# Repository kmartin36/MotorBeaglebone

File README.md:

# MotorBeaglebone
Motor drive cape for the Beaglebone Black featuring three channels, encoders, current sensors, and voltage sensing

This uses the High-Res PWM modules, the ADC, and the Enhanced Quadrature Encoder inputs.

See [this](https://github.com/Teknoman117/beaglebot/tree/master/encoders) repo for information on using the EQEP modules.

The new version is designed in kicad which features six channels and makes use of the DRV8873 motor driver IC. The three remaining quadrature encoder channels routed to the PRU pins for software decoding.

There is also a design based on the PocketBeagle with only four motors as the PocketBeagle only provies four of the 6 PWM modules on header pins.

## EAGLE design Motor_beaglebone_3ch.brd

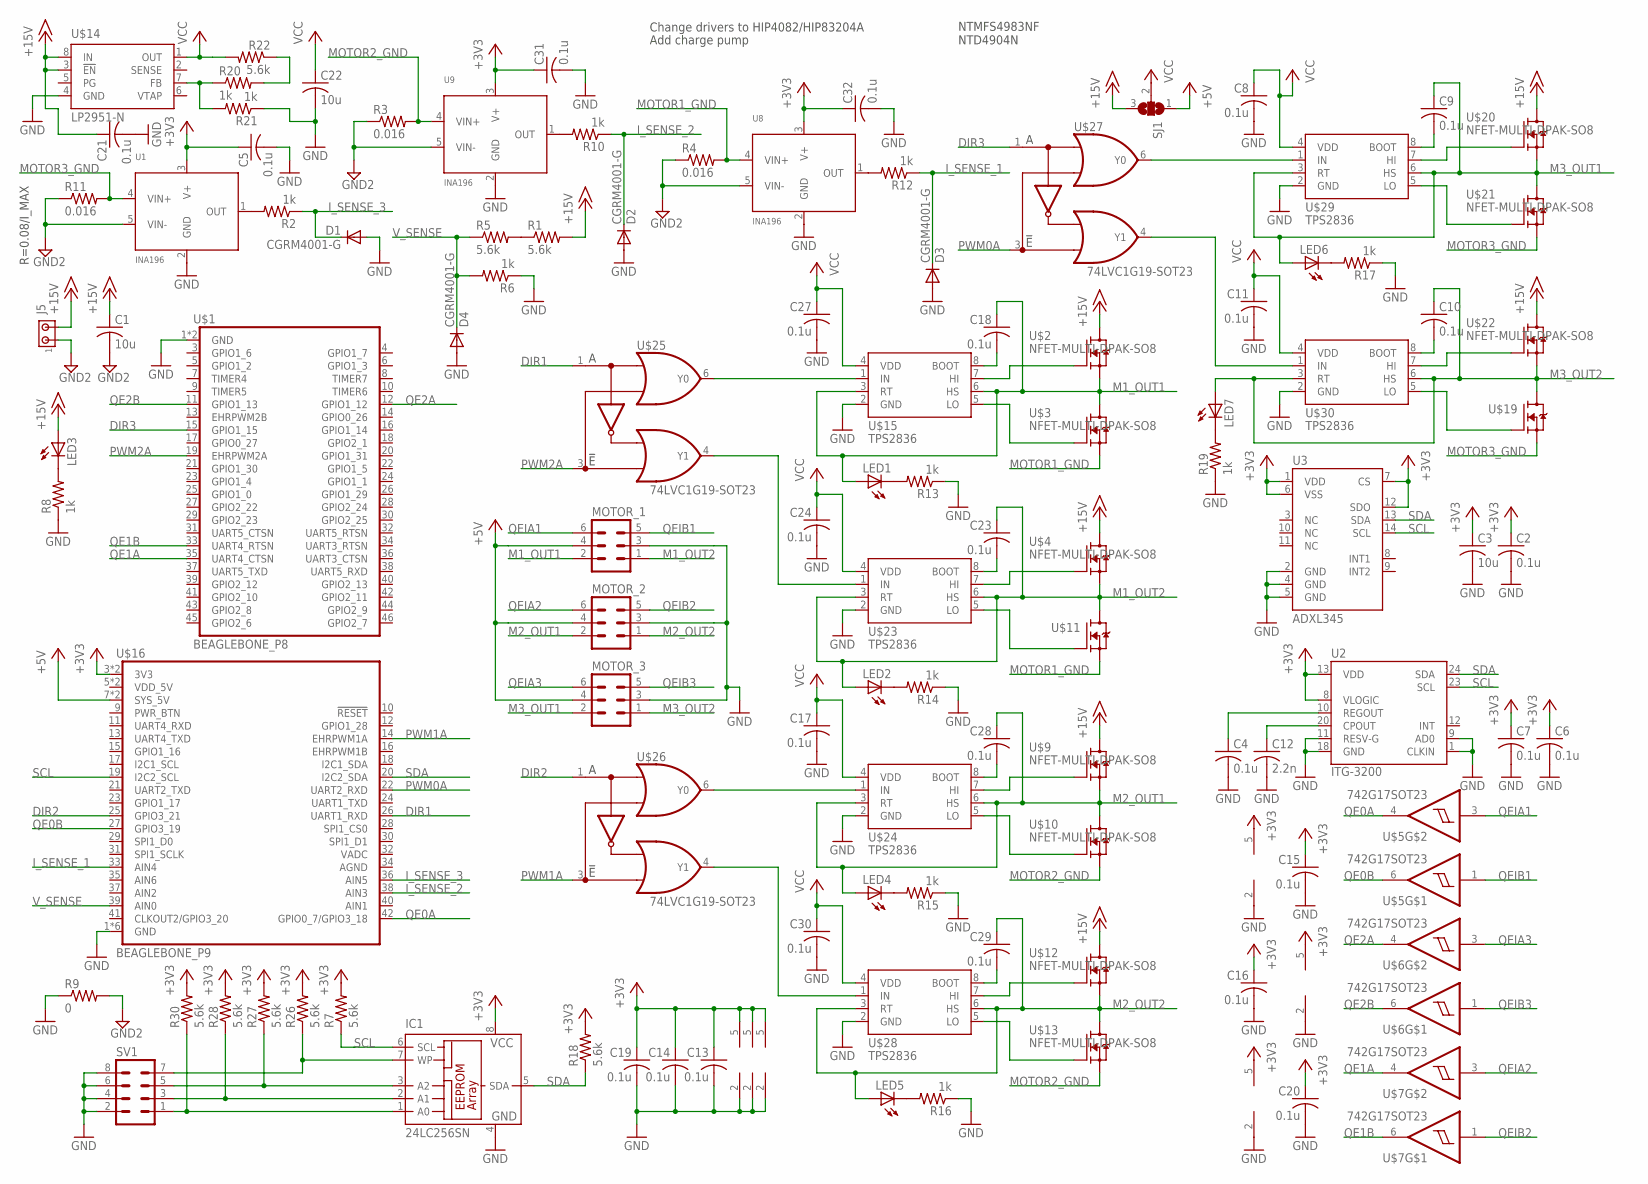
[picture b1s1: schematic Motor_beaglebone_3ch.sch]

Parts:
C1, C3, C22: 10u; C1206
C2, C4, C5, C6, C7, C8, C9, C10, C11, C13, C14, C15, C16, C17, C18, C19, C20, C21, C23, C24, C27, C28, C29, C30, C31, C32: 0.1u; C0603
C12: 2.2n; C0603
D1, D2, D3, D4: CGRM4001-G; SOD-123_MINI-SMA
IC1: 24LC256SN; SO-08
J5: MTA02-156; 1X2MTA
LED1, LED2, LED3, LED4, LED5, LED6, LED7: LED0603; LED-0603
MOTOR_1, MOTOR_2, MOTOR_3: MA03-2
R1, R5, R7, R18, R22, R26, R27, R28, R30: 5.6k; C0603
R2, R6, R8, R10, R12, R13, R14, R15, R16, R17, R19, R20, R21: 1k; C0603
R3, R4, R11: 0.016; C1206
R9: 0; C0603
SJ1: SJ2W; SJ_2
SV1: MA04-2
U1, U8, U9: INA196; SOT23-5
U2: ITG-3200; QFN-24
U3: ADXL345; LGA14
U$1: BEAGLEBONE_P8
U$2, U$3, U$4, U$9, U$10, U$11, U$12, U$13, U$19, U$20, U$21, U$22: NFET-MULTI-DPAK-SO8; DPAK-S08
U$5, U$6, U$7: 742G17SOT23; SOT23-6
U$14: LP2951-N; VSSOP8
U$15, U$23, U$24, U$28, U$29, U$30: TPS2836; SO-08
U$16: BEAGLEBONE_P9
U$25, U$26, U$27: 74LVC1G19-SOT23; SOT23-6

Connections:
+3V3: C2.1, C3.1, C5.1, C6.1, C7.1, C13.1, C14.1, C15.1, C16.1, C19.1, C20.1, C31.1, C32.1, IC1.8 (VCC), R7.2, R18.2, R26.2, R27.2, R28.2, R30.2, U1.3 (V+), U2.8 (VLOGIC), U2.13 (VDD), U3.1 (VDD), U3.6 (VSS), U3.7 (CS), U3.12 (SDO), U8.3 (V+), U9.3 (V+), U$5.5 (V+), U$6.5 (V+), U$7.5 (V+), U$16.3 (3V3), U$16.4 (3V3), U$25.5 (V+), U$26.5 (V+), U$27.5 (V+)
+5V: MOTOR_1.4, MOTOR_2.4, MOTOR_3.4, SJ1.1, U$16.7 (SYS_5V), U$16.8 (SYS_5V)
+15V: C1.1, C21.1, J5.2, LED3.A, R1.2, SJ1.3, U$2.2 (D), U$4.2 (D), U$9.2 (D), U$12.2 (D), U$14.3 (!EN), U$14.8 (IN), U$20.2 (D), U$22.2 (D)
DIR1: U$16.26 (UART1_RXD), U$25.1 (A)
DIR2: U$16.25 (GPIO3_21), U$26.1 (A)
DIR3: U$1.15 (GPIO1_15), U$27.1 (A)
GND: C2.2, C3.2, C4.2, C5.2, C6.2, C7.2, C8.2, C11.2, C12.2, C13.2, C14.2, C15.2, C16.2, C17.2, C19.2, C20.2, C21.2, C22.2, C24.2, C27.2, C30.2, C31.2, C32.2, D1.A, D2.A, D3.A, D4.A, IC1.4 (GND), MOTOR_1.3, MOTOR_2.3, MOTOR_3.3, R6.1, R8.1, R9.1, R13.1, R14.1, R15.1, R16.1, R17.1, R19.1, R21.1, SV1.2, SV1.4, SV1.6, SV1.8, U1.2 (GND), U2.1 (CLKIN), U2.9 (AD0), U2.11 (RESV-G), U2.18 (GND), U3.2 (GND), U3.4 (GND), U3.5 (GND), U8.2 (GND), U9.2 (GND), U$1.1 (GND), U$1.2 (GND), U$5.2 (V-), U$6.2 (V-), U$7.2 (V-), U$14.4 (GND), U$15.2 (GND), U$16.1 (GND), U$16.2 (GND), U$16.43 (GND), U$16.44 (GND), U$16.45 (GND), U$16.46 (GND), U$23.2 (GND), U$24.2 (GND), U$25.2 (V-), U$26.2 (V-), U$27.2 (V-), U$28.2 (GND), U$29.2 (GND), U$30.2 (GND)
GND2: C1.2, J5.1, R3.1, R4.1, R9.2, R11.1, U1.5 (VIN-), U8.5 (VIN-), U9.5 (VIN-)
I_SENSE_1: D3.C, R12.1, U$16.33 (AIN4)
I_SENSE_2: D2.C, R10.1, U$16.38 (AIN3)
I_SENSE_3: D1.C, R2.1, U$16.36 (AIN5)
M1_OUT1: C18.1, LED1.A, MOTOR_1.2, U$2.3 (S), U$2.4 (S), U$2.5 (S), U$2.6 (S), U$3.2 (D), U$15.3 (RT), U$15.6 (HS)
M1_OUT2: C23.1, LED2.A, MOTOR_1.1, U$4.3 (S), U$4.4 (S), U$4.5 (S), U$4.6 (S), U$11.2 (D), U$23.3 (RT), U$23.6 (HS)
M2_OUT1: C28.1, LED4.A, MOTOR_2.2, U$9.3 (S), U$9.4 (S), U$9.5 (S), U$9.6 (S), U$10.2 (D), U$24.3 (RT), U$24.6 (HS)
M2_OUT2: C29.1, LED5.A, MOTOR_2.1, U$12.3 (S), U$12.4 (S), U$12.5 (S), U$12.6 (S), U$13.2 (D), U$28.3 (RT), U$28.6 (HS)
M3_OUT1: C9.1, LED6.A, MOTOR_3.2, U$20.3 (S), U$20.4 (S), U$20.5 (S), U$20.6 (S), U$21.2 (D), U$29.3 (RT), U$29.6 (HS)
M3_OUT2: C10.1, LED7.A, MOTOR_3.1, U$19.2 (D), U$22.3 (S), U$22.4 (S), U$22.5 (S), U$22.6 (S), U$30.3 (RT), U$30.6 (HS)
MOTOR1_GND: R4.2, U8.4 (VIN+), U$3.3 (S), U$3.4 (S), U$3.5 (S), U$3.6 (S), U$11.3 (S), U$11.4 (S), U$11.5 (S), U$11.6 (S)
MOTOR2_GND: R3.2, U9.4 (VIN+), U$10.3 (S), U$10.4 (S), U$10.5 (S), U$10.6 (S), U$13.3 (S), U$13.4 (S), U$13.5 (S), U$13.6 (S)
MOTOR3_GND: R11.2, U1.4 (VIN+), U$19.3 (S), U$19.4 (S), U$19.5 (S), U$19.6 (S), U$21.3 (S), U$21.4 (S), U$21.5 (S), U$21.6 (S)
unnamed: IC1.3 (A2), R27.1, SV1.5
unnamed: IC1.2 (A1), R28.1, SV1.3
unnamed: IC1.1 (A0), R30.1, SV1.1
unnamed: IC1.7 (WP), R26.1, SV1.7
unnamed: R1.1, R5.2
unnamed: R2.2, U1.1 (OUT)
unnamed: R10.2, U9.1 (OUT)
unnamed: R12.2, U8.1 (OUT)
unnamed: U$2.1 (G), U$2.7 (G), U$15.7 (HI)
unnamed: U$3.1 (G), U$3.7 (G), U$15.5 (LO)
unnamed: LED1.C, R13.2
unnamed: LED2.C, R14.2
unnamed: LED3.C, R8.2
unnamed: C18.2, U$15.8 (BOOT)
unnamed: U$20.1 (G), U$20.7 (G), U$29.7 (HI)
unnamed: C28.2, U$24.8 (BOOT)
unnamed: U$21.1 (G), U$21.7 (G), U$29.5 (LO)
unnamed: C23.2, U$23.8 (BOOT)
unnamed: U$4.1 (G), U$4.7 (G), U$23.7 (HI)
unnamed: C9.2, U$29.8 (BOOT)
unnamed: U$11.1 (G), U$11.7 (G), U$23.5 (LO)
unnamed: C29.2, U$28.8 (BOOT)
unnamed: U$12.1 (G), U$12.7 (G), U$28.7 (HI)
unnamed: U$13.1 (G), U$13.7 (G), U$28.5 (LO)
unnamed: C10.2, U$30.8 (BOOT)
unnamed: U$9.1 (G), U$9.7 (G), U$24.7 (HI)
unnamed: U$10.1 (G), U$10.7 (G), U$24.5 (LO)
unnamed: U$22.1 (G), U$22.7 (G), U$30.7 (HI)
unnamed: U$19.1 (G), U$19.7 (G), U$30.5 (LO)
unnamed: C4.1, U2.10 (REGOUT)
unnamed: C12.1, U2.20 (CPOUT)
unnamed: LED4.C, R15.2
unnamed: LED5.C, R16.2
unnamed: LED6.C, R17.2
unnamed: LED7.C, R19.2
unnamed: R20.2, R22.1
unnamed: R20.1, R21.2, U$14.7 (FB)
unnamed: U$23.1 (IN), U$25.4 (Y1)
unnamed: U$15.1 (IN), U$25.6 (Y0)
unnamed: U$27.6 (Y0), U$29.1 (IN)
unnamed: U$27.4 (Y1), U$30.1 (IN)
unnamed: U$24.1 (IN), U$26.6 (Y0)
unnamed: U$26.4 (Y1), U$28.1 (IN)
PWM0A: U$16.22 (UART2_RXD), U$27.3 (!E)
PWM1A: U$16.14 (EHRPWM1A), U$26.3 (!E)
PWM2A: U$1.19 (EHRPWM2A), U$25.3 (!E)
QE0A: U$5.4 (O), U$16.42 (GPIO0_7/GPIO3_18)
QE0B: U$5.6 (O), U$16.27 (GPIO3_19)
QE1A: U$1.35 (UART4_CTSN), U$7.4 (O)
QE1B: U$1.33 (UART4_RTSN), U$7.6 (O)
QE2A: U$1.12 (GPIO1_12), U$6.4 (O)
QE2B: U$1.11 (GPIO1_13), U$6.6 (O)
QEIA1: MOTOR_1.6, U$5.3 (I)
QEIA2: MOTOR_2.6, U$7.3 (I)
QEIA3: MOTOR_3.6, U$6.3 (I)
QEIB1: MOTOR_1.5, U$5.1 (I)
QEIB2: MOTOR_2.5, U$7.1 (I)
QEIB3: MOTOR_3.5, U$6.1 (I)
SCL: IC1.6 (SCL), R7.1, U2.23 (SCL), U3.14 (SCL), U$16.19 (I2C2_SCL)
SDA: IC1.5 (SDA), R18.1, U2.24 (SDA), U3.13 (SDA), U$16.20 (I2C2_SDA)
VCC: C8.1, C11.1, C17.1, C22.1, C24.1, C27.1, C30.1, R22.2, SJ1.2, U$14.1 (OUT), U$15.4 (VDD), U$23.4 (VDD), U$24.4 (VDD), U$28.4 (VDD), U$29.4 (VDD), U$30.4 (VDD)
V_SENSE: D4.C, R5.1, R6.2, U$16.39 (AIN0)

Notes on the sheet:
R=0.08/I_MAX
NTMFS4983NF NTD4904N
Change drivers to HIP4082/HIP83204A
Add charge pump

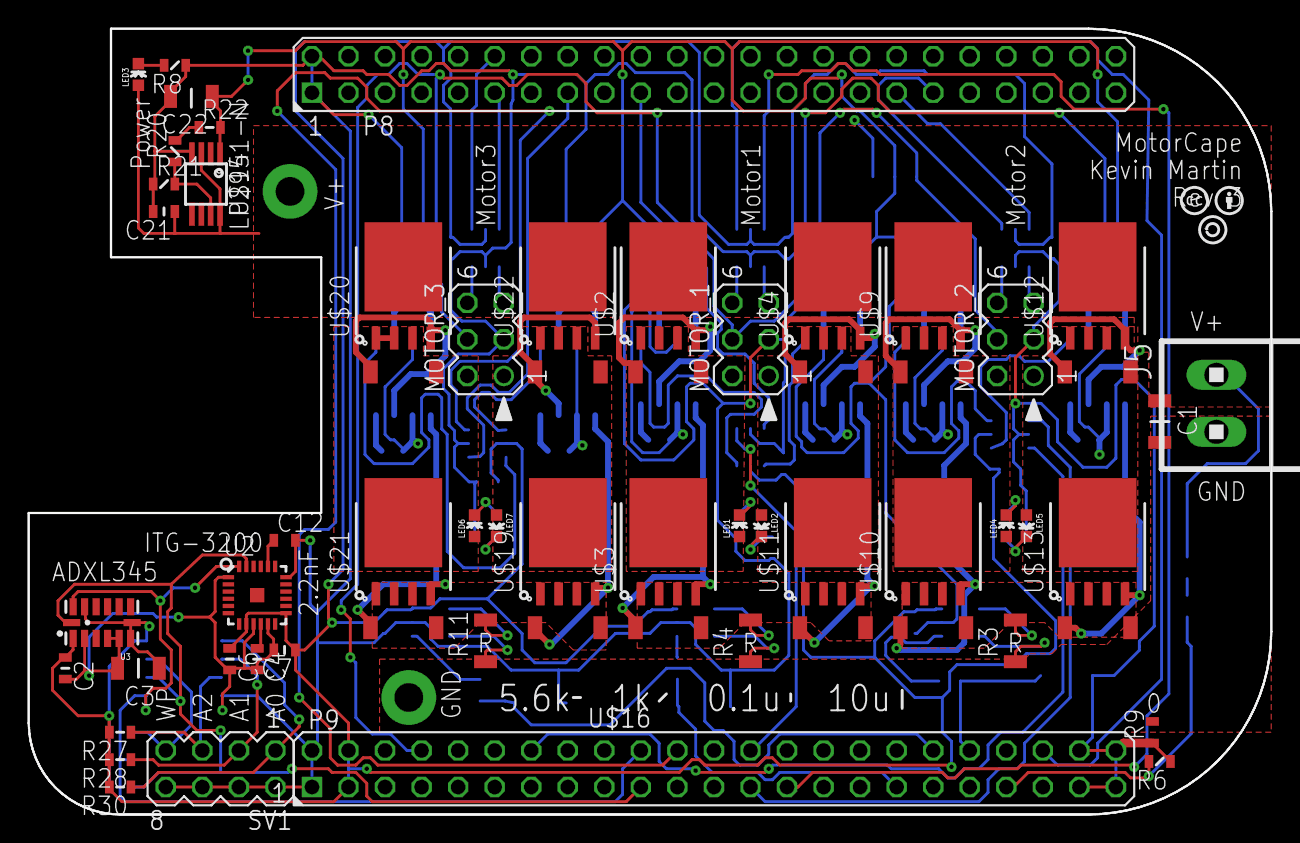
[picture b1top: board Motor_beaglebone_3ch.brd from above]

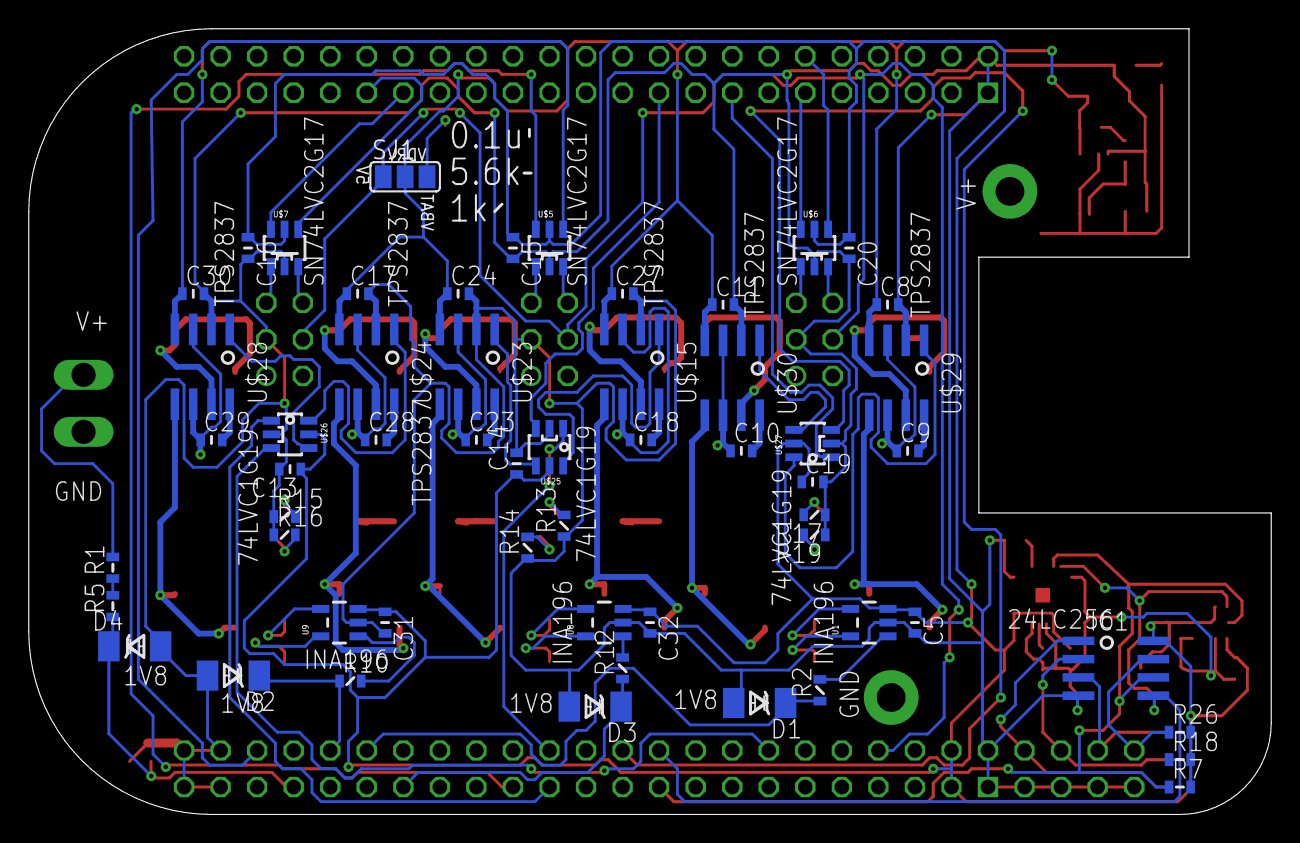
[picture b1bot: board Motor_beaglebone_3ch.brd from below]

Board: 2 copper layers, 86.4 x 54.6 mm, 106 parts (56 on the bottom side), 82 nets.

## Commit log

2015-03-15 Using CC-BY-SA license
2015-03-15 Adding info to the README file
2015-03-15 Correcting syntax
2019-11-23 Modified P9 to use pins 1-46 instead of 47-92
2019-11-23 New design with DRV8873s and using kicad
2019-11-23 Updated README for the new board designs
2019-11-24 Fixing paths to libraries
2019-11-24 routing
2019-11-27 Routing 1st draft
2019-11-28 Added thermal planes Improved routing Increased width of power traces where possible
2019-11-28 Updated 3D models
2019-11-29 Adding the pin spreadsheet
2019-11-30 Changed pins in schematic 8 servos Fixed paths
2019-12-09 More routing
2019-12-11 Routing 1st pass complete
2019-12-11 Wider traces for power nets
2019-12-28 Wider motor traces
2019-12-28 Cleaning up traces
2020-02-20 Adding python motor control-over-http code
2020-03-17 More space for power traces
2020-07-20 Widened traces for V+ to motor drivers Added VIA stitching to V+ and GND planes V+ trace widths set using +60C, 5A, and 2oz copper
2020-07-20 Widened GND traces to motor drivers GND trace width determined using +60C, 5A, and 2oz copper
2020-07-25 Added top and bottom heatsink planes Added thermal vias between ground planes
2020-07-26 Beginning silkscreen
2020-07-26 Moved silkscreen to B.SilkS layer because silkscreen in libraries cannot be modified Silkscreen 1.0 complete
2020-07-27 Added a few more thermal vias Cleaned up the silkscreen
2020-07-27 Changed capacitor values to include voltage ratings Changed TBD resistors to RA/RB for upper and lower divider resistors
2020-07-27 Improved heatsink area Improved silkscreen
2020-07-27 Modified DRC to OSH Park 2oz requirements Most traces fail DRC
2020-07-27 Adding gerbers
2020-07-27 Moved items to at least 15mil from the outline
2020-07-27 Updated gerbers to latest
2022-07-05 Modified to 6/6 trace/space to allow Oshpark production
2022-09-24 Replaced large vias with 2 normal small vias Reduced via size to 20/10 to match OshPark
2022-09-26 Updated top silkscreen gerber file to indicate that it is the top instead of the bottom

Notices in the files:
parts and their libraries:
SparkFun-LED: Licensing: CC v3.0 Share-Alike You are welcome to use this library for commercial purposes.
